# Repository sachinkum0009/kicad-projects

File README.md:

# kicad-projects
kicad projects repo

### List of Projects

1. **Power Supply**

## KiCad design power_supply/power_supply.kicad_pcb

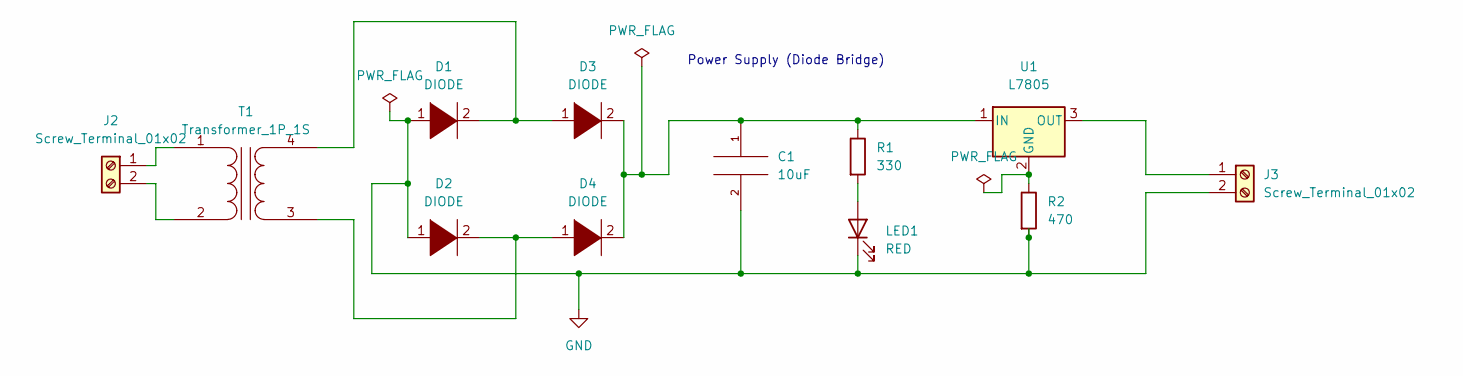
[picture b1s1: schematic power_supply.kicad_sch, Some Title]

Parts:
C1: 10uF; CP_Radial_D10.0mm_P3.80mm
D1, D2, D3, D4: DIODE; D_A-405_P7.62mm_Horizontal
J2, J3: Screw_Terminal_01x02; TerminalBlock_Altech_AK300-2_P5.00mm
LED1: RED; LED_D3.0mm
R1: 330; R_Axial_DIN0204_L3.6mm_D1.6mm_P5.08mm_Horizontal
R2: 470; R_Axial_DIN0204_L3.6mm_D1.6mm_P5.08mm_Horizontal
T1: Transformer_1P_1S; Transformer_CHK_EI48-8VA_1xSec
U1: L7805

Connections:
GND: C1.2, D1.1 (K), D2.1 (K), J3.2, LED1.1 (K), R2.2
unnamed: C1.1, D3.2 (A), D4.2 (A), R1.1, U1.1 (IN)
unnamed: D1.2 (A), D3.1 (K), T1.4 (SB)
unnamed: D2.2 (A), D4.1 (K), T1.3 (SA)
unnamed: LED1.2 (A), R1.2
unnamed: R2.1, U1.2 (GND)
unnamed: J2.1, T1.1 (AA)
unnamed: J2.2, T1.2 (AB)
unnamed: J3.1, U1.3 (OUT)

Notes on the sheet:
Power Supply (Diode Bridge)

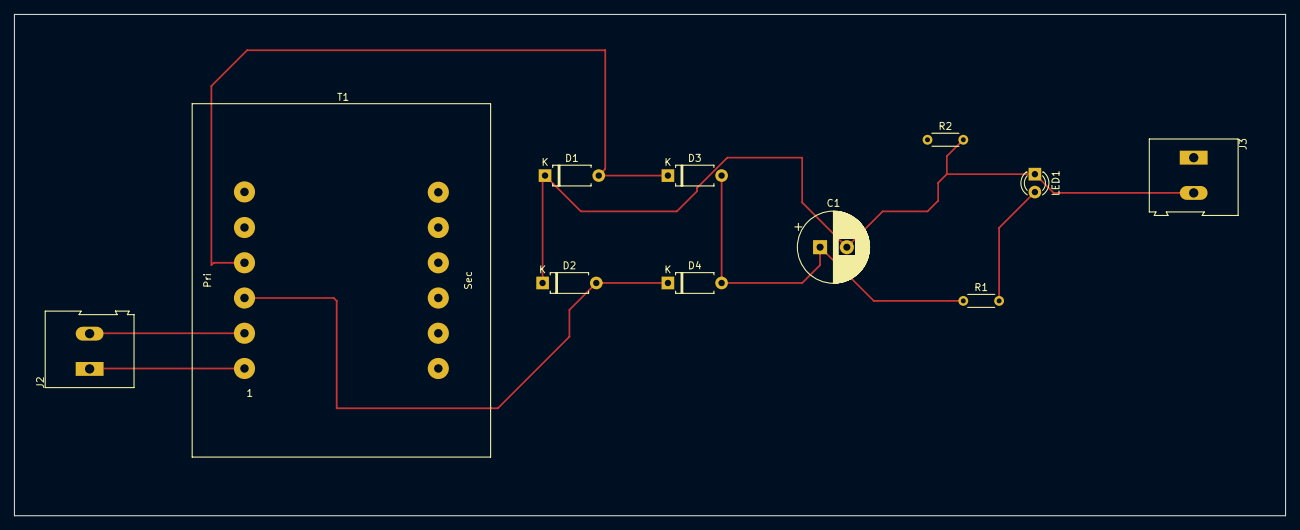
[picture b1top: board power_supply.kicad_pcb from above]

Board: 2 copper layers, 180.3 x 71.1 mm, 11 parts (0 on the bottom side), 7 nets.

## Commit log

2023-02-14 gitignore updated
2023-02-14 power supply project added
2023-02-14 readme updated
